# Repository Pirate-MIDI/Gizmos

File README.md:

Welcome to our open source collection of Gizmos! 🚀

Gizmos are cool little devices that we just wanted to build, and thought you might like to come along for the ride. 
They're not designed to be hardcore consumer-grade products. They're handy projects that we wanted to give to you to work with. 

If you want to modify the design, go for it. If you want to create an accessory for a Gizmo, go for it! 

If you want to give others access to what you've created, create a pull request and we'll add it into the repository for others to see and use. 

## All About Community
All our consumer products are centred on the needs and wants of our community. 
Who knows? Perhaps interest in a Gizmo will spawn an amazing new PIRATE MIDI device. 

Feel free to email **support@piratemidi.com** with any enquiries you might have. We're always happy to help out. 

## Discussions & Issues
Please use the [Discussions](https://github.com/Pirate-MIDI/Gizmos/discussions) tab here on Github to communicate with other community members about the Gizmos, ideas, etc. 

If you have a problem with something in the Gizmo repository, you can log it as an [issue](https://github.com/Pirate-MIDI/Gizmos/issues)

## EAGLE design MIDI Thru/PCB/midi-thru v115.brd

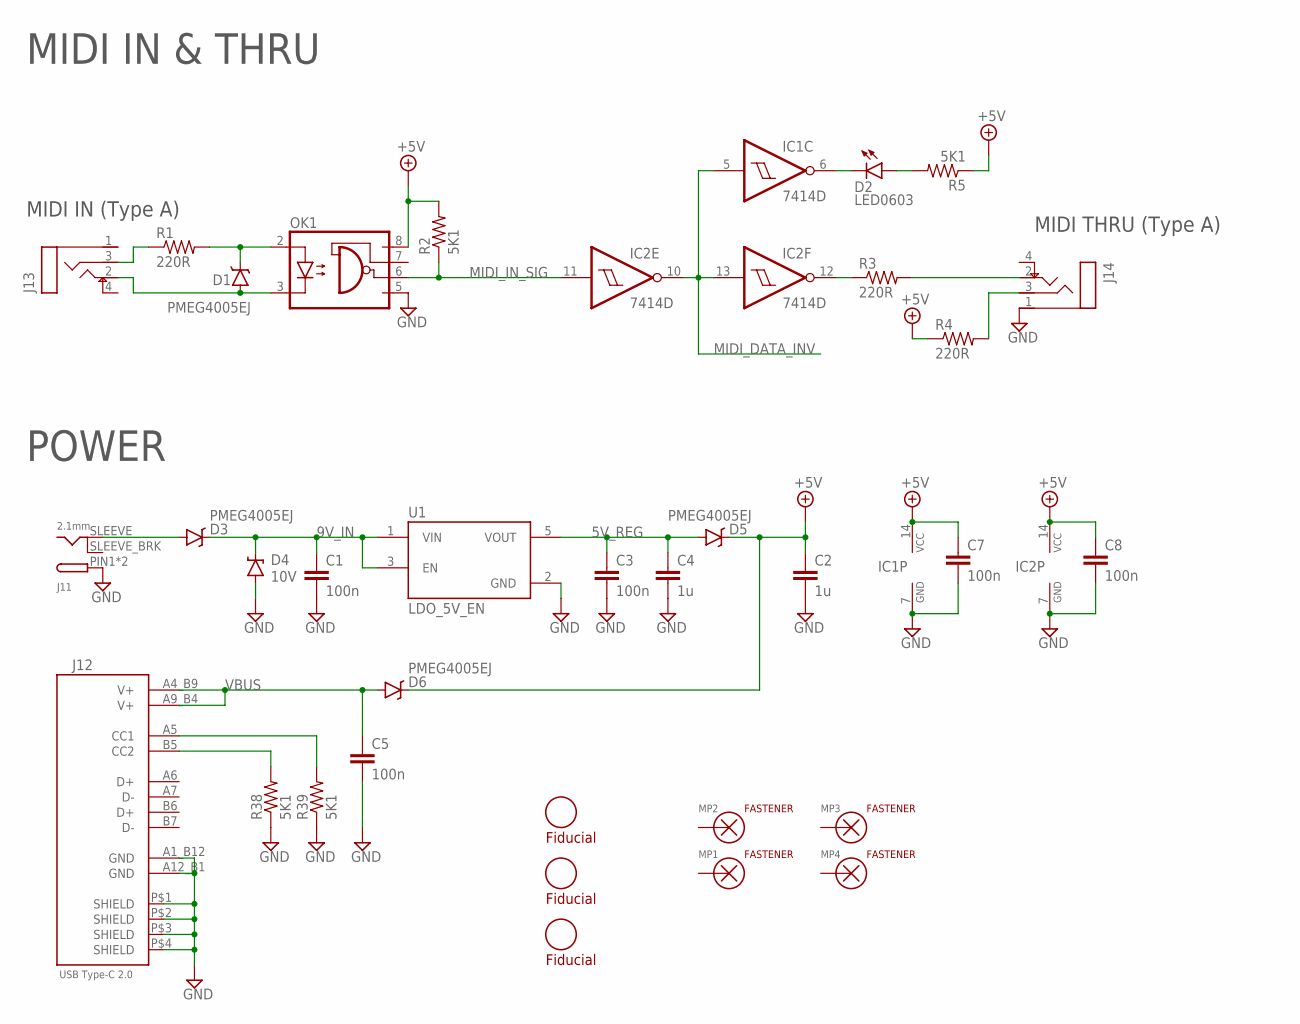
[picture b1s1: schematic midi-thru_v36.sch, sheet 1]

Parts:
C1, C3, C5, C7, C8: 100n; 0603_CAP
C2, C4: 1u; 0603_CAP
D1, D3, D5, D6: PMEG4005EJ; SOD-323
D2: LED0603; CHIPLED_0603
D4: 10V; SOD-323
FD1, FD2, FD3: FIDUCIALROUND_1MM; FIDUCIAL_ROUND_1MM
IC1, IC2: 7414D; SO14
J11: 2.1mm; DCJACK_2MM_SMT
J12: USB_TYPE-C_2.0; 12402012E212A
J13, J14: TRS-TIP-SW3.5MM1; PJ-327C-4A
MP1, MP2, MP3, MP4: SCREW-FASTENER3; M3-PANHEAD-VIA
OK1: 6N137; SMD8
R1, R3, R4: 220R; 0603-RES
R2, R5, R38, R39: 5K1; 0603-RES
U1: LDO_5V_EN; SOT23-5

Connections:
5V_REG: C3.1, C4.1, D5.A, U1.5 (VOUT)
9V_IN: C1.1, D3.C, D4.C, U1.1 (VIN), U1.3 (EN)
+5V: C2.1, C7.1, C8.1, D5.C, D6.C, IC1.14 (VCC), IC2.14 (VCC), OK1.8 (VCC), R2.2, R4.1, R5.1; also elsewhere on the board
CONNECT: J11.SLEEVE_BRK (CONNECT)
GND: C1.2, C2.2, C3.2, C4.2, C5.2, C7.2, C8.2, D4.A, IC1.7 (GND), IC2.7 (GND), J11.PIN1 (PIN), J11.PIN2 (PIN), J12.A1_B12 (GND), J12.A12_B1 (GND), J12.P$1 (SHIELD), J12.P$2 (SHIELD), J12.P$3 (SHIELD), J12.P$4 (SHIELD), J14.1 (S), OK1.5 (GND), R38.1, R39.1, U1.2 (GND); also elsewhere on the board
MIDI_DATA_INV: IC1.5 (I), IC2.10 (O), IC2.13 (I); also elsewhere on the board
MIDI_IN_SIG: IC2.11 (I), OK1.6 (VO), R2.1
unnamed: J13.3 (R), R1.1
unnamed: D1.A, J13.2 (T), OK1.3 (C)
unnamed: D1.C, OK1.2 (A), R1.2
unnamed: IC2.12 (O), R3.1
unnamed: J14.2 (T), R3.2
unnamed: J14.3 (R), R4.2
unnamed: D2.C, IC1.6 (O)
unnamed: D2.A, R5.2
unnamed: D3.A, J11.SLEEVE
unnamed: J12.A5 (CC1), R39.2
unnamed: J12.B5 (CC2), R38.2
VBUS: C5.1, D6.A, J12.A4_B9 (V+), J12.A9_B4 (V+)

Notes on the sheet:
MIDI IN (Type A)
MIDI THRU (Type A)
MIDI IN & THRU
POWER

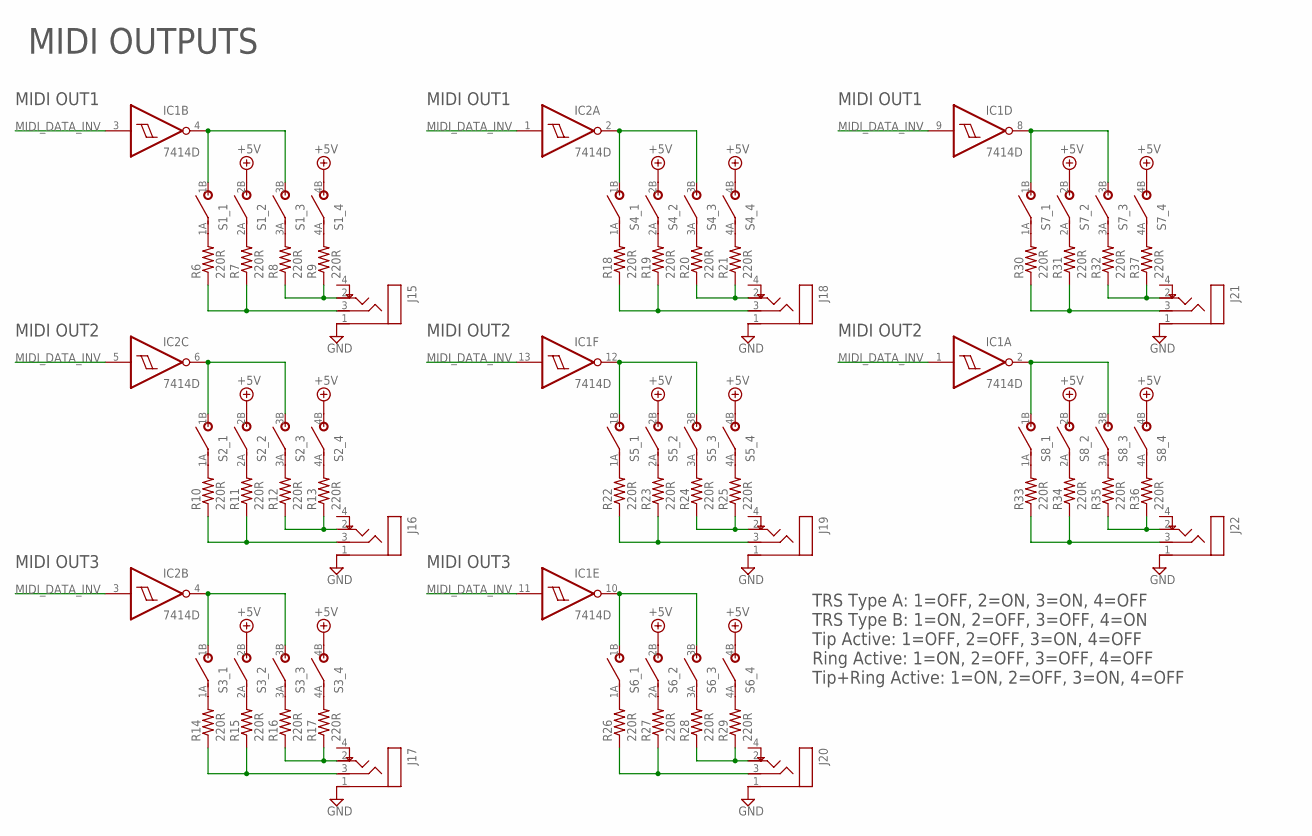
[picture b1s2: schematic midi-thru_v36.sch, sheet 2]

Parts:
IC1, IC2: 7414D; SO14
J15, J16, J17, J18, J19, J22: TRS-TIP-SW; PJ-327C-4A
J20, J21: TRS-TIP-SW3.5MM1; PJ-327C-4A
R6, R7, R8, R9, R10, R11, R12, R13, R14, R15, R16, R17, R18, R19, R20, R21, R22, R23, R24, R25, R26, R27, R28, R29, R30, R31, R32, R33, R34, R35, R36, R37: 220R; 0603-RES
S1, S2, S3, S4, S5, S6, S7, S8: DIPSW_4SMD; DIP4_2.54

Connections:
+5V: S1.2B (S), S1.4B (S), S2.2B (S), S2.4B (S), S3.2B (S), S3.4B (S), S4.2B (S), S4.4B (S), S5.2B (S), S5.4B (S), S6.2B (S), S6.4B (S), S7.2B (S), S7.4B (S), S8.2B (S), S8.4B (S); also elsewhere on the board
GND: J15.1 (S), J16.1 (S), J17.1 (S), J18.1 (S), J19.1 (S), J20.1 (S), J21.1 (S), J22.1 (S); also elsewhere on the board
MIDI_DATA_INV: IC1.1 (I), IC1.3 (I), IC1.9 (I), IC1.11 (I), IC1.13 (I), IC2.1 (I), IC2.3 (I), IC2.5 (I); also elsewhere on the board
unnamed: J16.3 (R), R10.1, R11.1
unnamed: J15.3 (R), R6.1, R7.1
unnamed: R6.2, S1.1A
unnamed: R7.2, S1.2A
unnamed: J15.2 (T), R8.1, R9.1
unnamed: R8.2, S1.3A
unnamed: R9.2, S1.4A
unnamed: IC1.4 (O), S1.1B (S), S1.3B (S)
unnamed: J16.2 (T), R12.1, R13.1
unnamed: R10.2, S2.1A
unnamed: R11.2, S2.2A
unnamed: R12.2, S2.3A
unnamed: R13.2, S2.4A
unnamed: IC2.6 (O), S2.1B (S), S2.3B (S)
unnamed: J17.3 (R), R14.1, R15.1
unnamed: J17.2 (T), R16.1, R17.1
unnamed: IC2.4 (O), S3.1B (S), S3.3B (S)
unnamed: R14.2, S3.1A
unnamed: R15.2, S3.2A
unnamed: R16.2, S3.3A
unnamed: R17.2, S3.4A
unnamed: J18.3 (R), R18.1, R19.1
unnamed: J18.2 (T), R20.1, R21.1
unnamed: R18.2, S4.1A
unnamed: R19.2, S4.2A
unnamed: R20.2, S4.3A
unnamed: R21.2, S4.4A
unnamed: IC2.2 (O), S4.1B (S), S4.3B (S)
unnamed: J19.3 (R), R22.1, R23.1
unnamed: J19.2 (T), R24.1, R25.1
unnamed: R22.2, S5.1A
unnamed: R23.2, S5.2A
unnamed: R24.2, S5.3A
unnamed: R25.2, S5.4A
unnamed: IC1.12 (O), S5.1B (S), S5.3B (S)
unnamed: J20.3 (R), R26.1, R27.1
unnamed: J20.2 (T), R28.1, R29.1
unnamed: IC1.10 (O), S6.1B (S), S6.3B (S)
unnamed: R26.2, S6.1A
unnamed: R27.2, S6.2A
unnamed: R28.2, S6.3A
unnamed: R29.2, S6.4A
unnamed: J21.3 (R), R30.1, R31.1
unnamed: J21.2 (T), R32.1, R37.1
unnamed: IC1.8 (O), S7.1B (S), S7.3B (S)
unnamed: J22.3 (R), R33.1, R34.1
unnamed: J22.2 (T), R35.1, R36.1
unnamed: IC1.2 (O), S8.1B (S), S8.3B (S)
unnamed: R30.2, S7.1A
unnamed: R31.2, S7.2A
unnamed: R32.2, S7.3A
unnamed: R33.2, S8.1A
unnamed: R34.2, S8.2A
unnamed: R35.2, S8.3A
unnamed: R36.2, S8.4A
unnamed: R37.2, S7.4A

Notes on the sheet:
MIDI OUT1
MIDI OUT2
MIDI OUT3
MIDI OUTPUTS
TRS Type A: 1=OFF, 2=ON, 3=ON, 4=OFF TRS Type B: 1=ON, 2=OFF, 3=OFF, 4=ON Tip Active: 1=OFF, 2=OFF, 3=ON, 4=OFF Ring Active: 1=ON, 2=OFF, 3=OFF, 4=OFF Tip+Ring Active: 1=ON, 2=OFF, 3=ON, 4=OFF

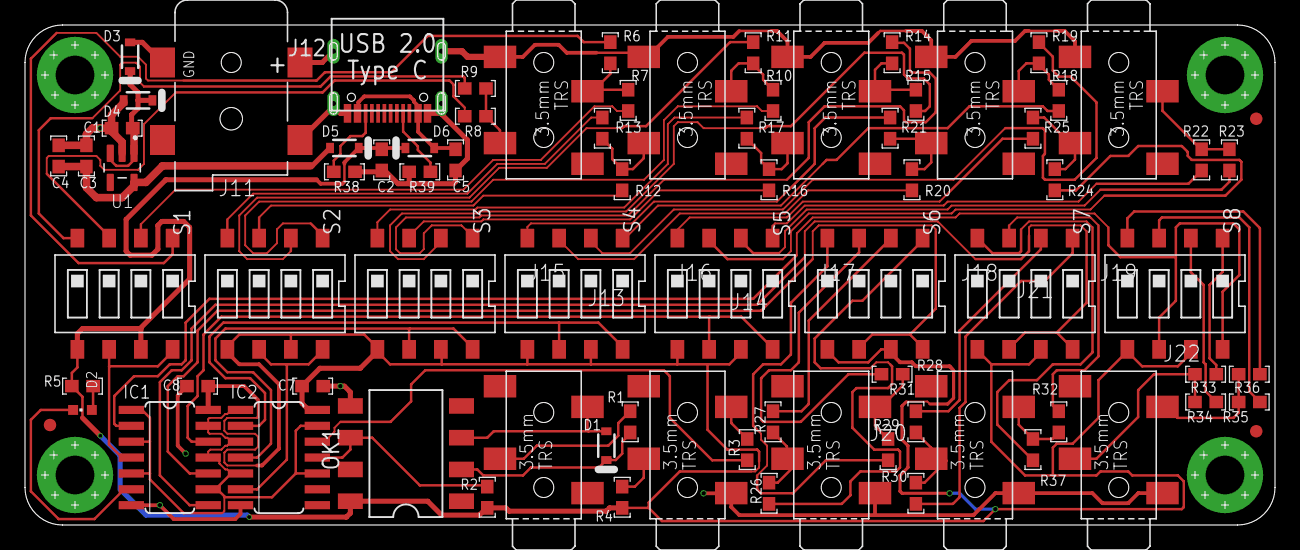
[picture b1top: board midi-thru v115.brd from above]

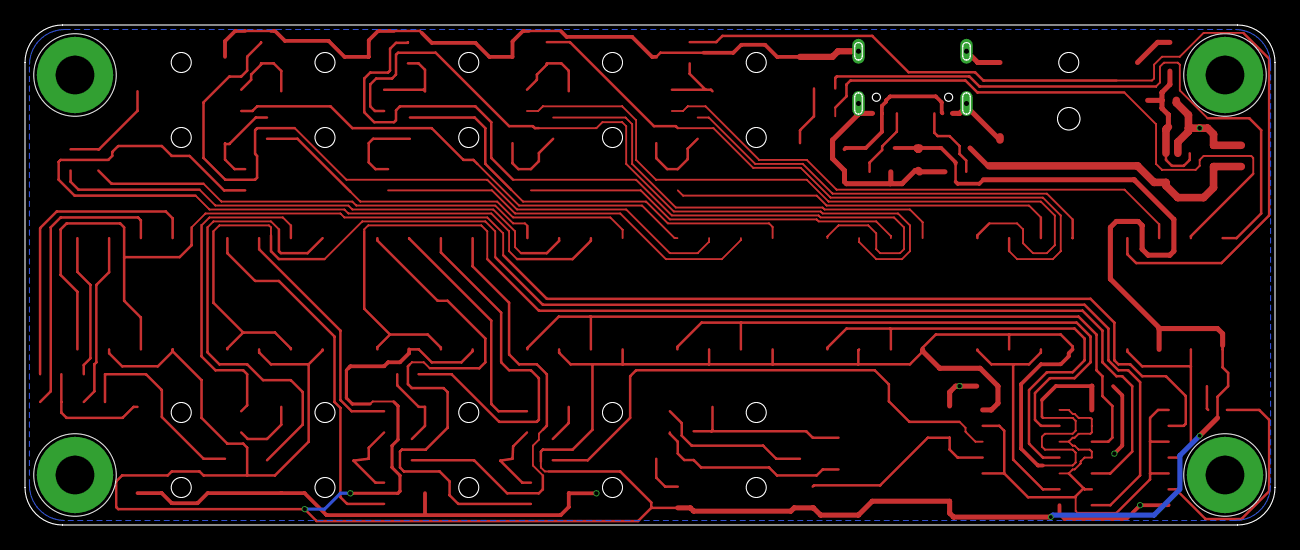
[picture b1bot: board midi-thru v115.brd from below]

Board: 2 copper layers, 100.0 x 40.0 mm, 86 parts (3 on the bottom side), 74 nets.

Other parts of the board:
U$1: PM_M_MAIN_LOGO1_STOP
U$2: MIDI_THRU_LOGO
U$4: MIDI_THRU_STOP_DM

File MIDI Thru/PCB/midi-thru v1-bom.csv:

"Qty";"Value";"Device";"Package";"Parts";"Description";"AVAILABILITY";"DESCRIPTION";"DIELECTRIC";"MANUFACTURER";"MF";"MP";"PACKAGE";"PART_NO";"PRICE";"SUPPLIER";"TOLERANCE";"VALUE";"VOLTAGE";
"8";"";"DIPSW_4SMD";"DIP4_2.54";"S1, S2, S3, S4, S5, S6, S7, S8";"Small compact SPST switches in a Dual In-Line (DIP) package. Useful for digital inputs, or adjusting individual circuit elements.";"";"";"";"";"";"";"";"";"";"";"";"";"";
"1";"";"USB_TYPE-C_2.0";"12402012E212A";"J12";"JAE DX07S024JJ2 USB Type-C Connector";"";"";"";"AMPHENOL";"";"";"";"12402012E212A";"";"MOUSER";"";"";"";
"5";"100n";"SMD-NP0603-100N-H";"0603_CAP";"C1, C3, C5, C7, C8";"General usage non-polarized capacitors.";"";"";"X7R";"YAGEO";"";"";"";"CC0603KRX7R9BB104";"";"MOUSER";"10%";"100n";"50V";
"1";"10V";"DIODE-ZENER10V";"SOD-323";"D4";"Zener Diode";"";"";"";"";"";"";"";"MM3Z10VST1G";"";"MOUSER";"";"";"";
"1";"1N4148";"1N4148";"SOD-323";"D1";"Fast Switching Diode";"";"";"";"MICRO COMMERCIAL COMPONENTS";"";"";"";"1N4148WX-TP";"";"MOUSER";"";"1N4148";"";
"2";"1u";"SMD-NP0603-1U-H";"0603_CAP";"C2, C4";"General usage non-polarized capacitors.";"";"";"X5R";"YAGEO";"";"";"";"CC0603KRX5R9BB105";"";"MOUSER";"10%";"1u";"50V";
"1";"2.1mm";"DCSMT";"DCJACK_2MM_SMT";"J11";"DC Jack";"";"";"";"TENSILITY INTERNATIONAL CORP";"";"";"";"54-00164";"";"DIGIKEY";"";"2.1mm";"";
"35";"220R";"US0603-220R";"0603-RES";"R1, R3, R4, R6, R7, R8, R9, R10, R11, R12, R13, R14, R15, R16, R17, R18, R19, R20, R21, R22, R23, R24, R25, R26, R27, R28, R29, R30, R31, R32, R33, R34, R35, R36, R37";"Standard resistor package for most 1/4W (6mm) resistors. Suitable for both carbon and metal film type resistors. Package layouts vary between 1-6 0.1" hole spacings.";"";"";"";"YAGEO";"";"";"";"RC0603FR-07220RL";"";"MOUSER";"";"220R";"";
"4";"5K1";"US0603-5K1";"0603-RES";"R2, R5, R38, R39";"Standard resistor package for most 1/4W (6mm) resistors. Suitable for both carbon and metal film type resistors. Package layouts vary between 1-6 0.1" hole spacings.";"";"";"";"YAGEO";"";"";"";"RC0603FR-075K1L";"";"MOUSER";"";"5K1";"";
"1";"6N137";"6N137S";"SMD8";"OK1";"MOTOROLA OPTO COUPLER";"";"";"";"LITE-ON";"";"";"";"6N137S";"";"MOUSER";"";"6N137";"";
"2";"7414D";"7414D";"SO14";"IC1, IC2";"Hex schmitt trigger INVERTER";"";"";"";"";"";"";"";"";"";"";"";"";"";
"3";"FIDUCIALROUND_1MM";"FIDUCIALROUND_1MM";"FIDUCIAL_ROUND_1MM";"FD1, FD2, FD3";"";"";"";"";"";"";"";"";"";"";"";"";"";"";
"1";"LED0603";"LED0603";"CHIPLED_0603";"D2";"";"";"";"";"";"";"";"";"";"";"";"";"";"";
"1";"MIC5504-3.3YM5_TR";"MIC5504-3.3YM5_TR";"SOT95P280X145-5N";"U1";"Linear Voltage Regulator IC 1 Output 300mA SOT-23-5  Check prices";"No availability data";" Linear Voltage Regulator IC 1 Output 300mA SOT-23-5 ";"";"";"Microchip";"MIC5504-3.3YM5 TR";"SOT-23 Microchip";"";"None";"";"";"";"";
"3";"PMEG4005EJ";"DIODE-SCHOTTKY-PMEG4005EJ";"SOD-323";"D3, D5, D6";"Schottky diodes in SFE's production catalog";"";"";"";"";"";"";"";"PMEG4005EJ,115";"";"Mouser";"";"PMEG4005EJ";"";
"4";"SCREW-FASTENER3";"SCREW-FASTENER3";"M3-PANHEAD-VIA";"MP1, MP2, MP3, MP4";"";"";"";"";"";"";"";"";"";"";"";"";"";"";
"10";"TRS-TIP-SW";"TRS-TIP-SW";"PJ-327C-4A";"J13, J14, J15, J16, J17, J18, J19, J20, J21, J22";"";"";"";"";"";"";"";"";"";"";"";"";"";"";

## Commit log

2021-09-28 Firmware Update
    Primitive bank settings response with updated JSON format
2022-05-09 First Gizmo!
    Removed old files and created first Gizmo folder for MIDI Thru.
2022-05-09 Updated drawing
2022-06-10 MIDI Thru Update
2022-06-10 MIDI Thru Hardware Update
2022-06-10 Rename Start Here.md to README.md
